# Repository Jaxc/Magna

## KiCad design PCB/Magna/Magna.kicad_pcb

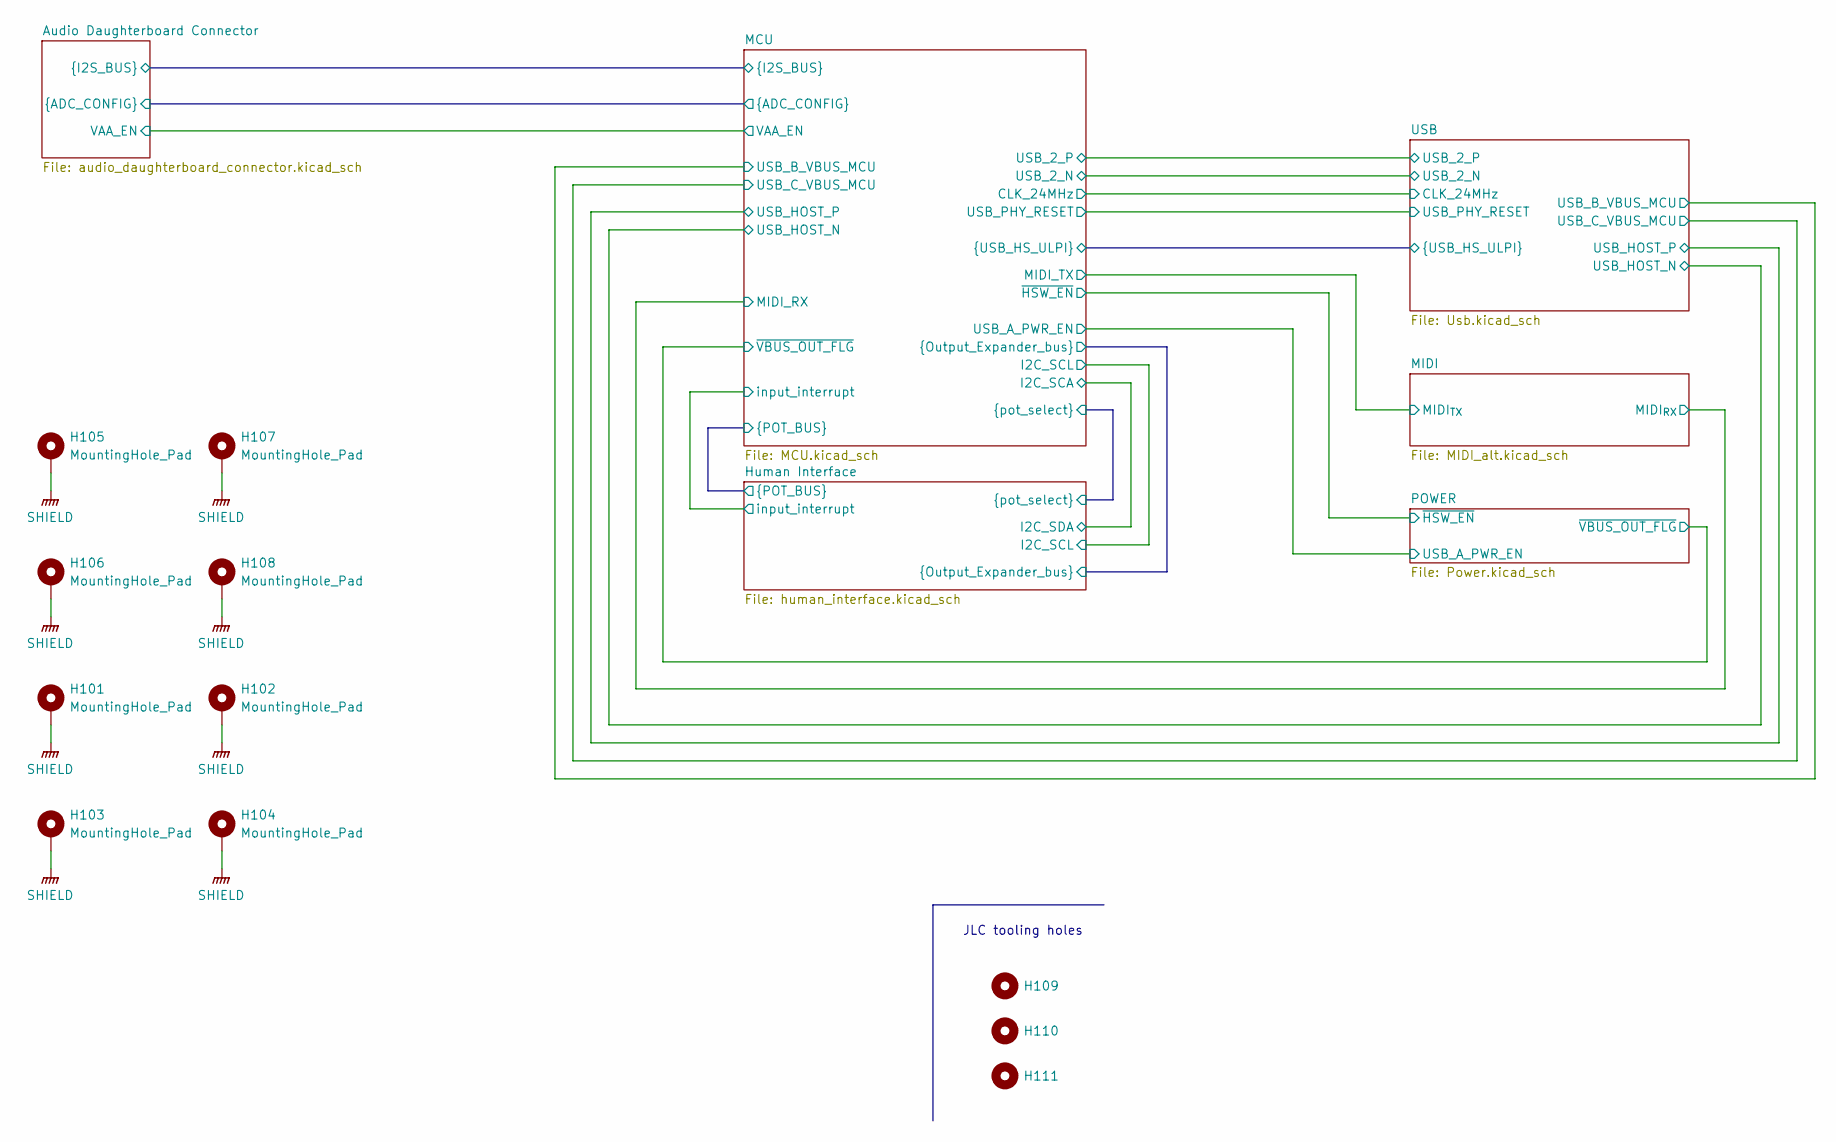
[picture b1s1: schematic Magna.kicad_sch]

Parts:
H101, H102, H103, H104, H105, H106, H107, H108: MountingHole_Pad; MountingHole_3.2mm_M3_Pad_Via
H109, H110, H111: MountingHole; ToolingHole_1.152mm

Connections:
SHIELD: H101.1, H102.1, H103.1, H104.1, H105.1, H106.1, H107.1, H108.1; also elsewhere on the board

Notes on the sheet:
JLC tooling holes

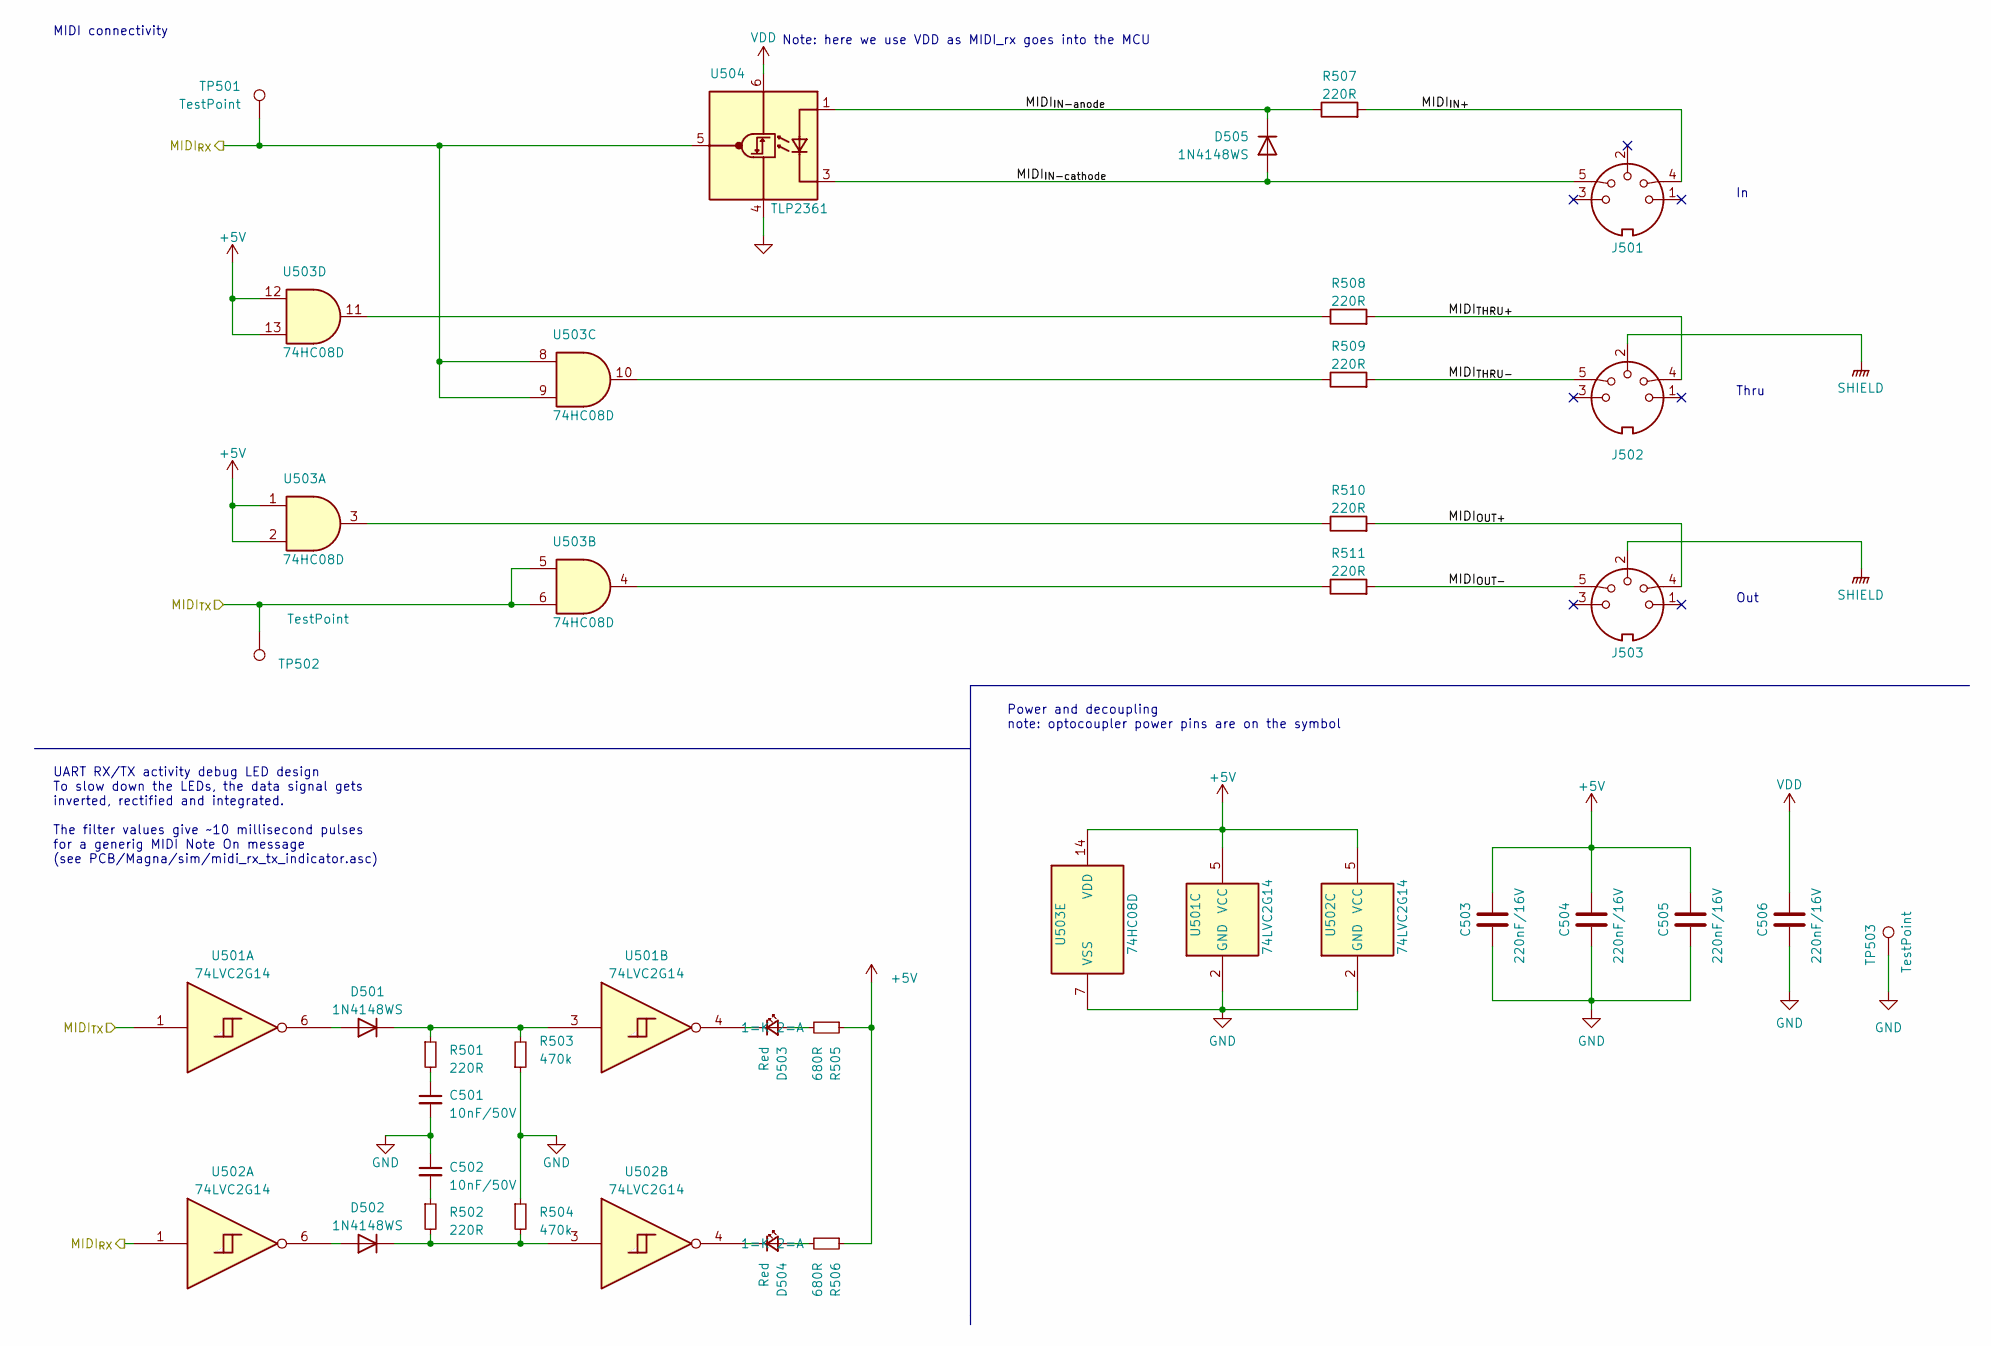
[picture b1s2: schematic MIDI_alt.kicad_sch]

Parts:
C501, C502: 10nF/50V; C_0805_2012Metric_Pad1.18x1.45mm_HandSolder; LCSC C1710
C503, C504, C505, C506: 220nF/16V; C_0402_1005Metric_Pad0.74x0.62mm_HandSolder; LCSC C16772
D501, D502, D505: 1N4148WS; D_SOD-523; LCSC C81598
D503, D504: Red; D_0805_2012Metric_Pad1.15x1.40mm_HandSolder; LCSC C84256
J501, J502, J503: DIN-5_180degree; DIN-504-M10; LCSC C2939344
R501, R502, R507, R508, R509, R510, R511: 220R; R_0805_2012Metric_Pad1.20x1.40mm_HandSolder; LCSC C17557
R503, R504: 470k; R_0805_2012Metric_Pad1.20x1.40mm_HandSolder; LCSC C17709
R505, R506: 680R; R_0805_2012Metric_Pad1.20x1.40mm_HandSolder; LCSC C17798
TP501, TP502, TP503: TestPoint; TestPoint_Keystone_5000-5004_Miniature
U501, U502: 74LVC2G14; SOT-363_SC-70-6_Handsoldering; LCSC C362110
U503: 74HC08D; SOIC-14_3.9x8.7mm_P1.27mm; LCSC C5593
U504: TLP2361; SO-6L_10x3.84mm_P1.27mm; LCSC C107626

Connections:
+5V: C503.1, C504.1, C505.1, R505.1, R506.1, U501.5 (VCC), U502.5 (VCC), U503.1, U503.2, U503.12, U503.13, U503.14 (VDD); also elsewhere on the board
/MCU/MIDI_RX: TP501.1, U502.1, U503.8, U503.9, U504.5 (VO); also elsewhere on the board
/MCU/MIDI_TX: TP502.1, U501.1, U503.5, U503.6; also elsewhere on the board
/MIDI/MIDI_{IN+}: J501.4, R507.2
/MIDI/MIDI_{IN-anode}: D505.1 (K), R507.1, U504.1 (A)
/MIDI/MIDI_{IN-cathode}: D505.2 (A), J501.5, U504.3 (K)
/MIDI/MIDI_{OUT+}: J503.4, R510.2
/MIDI/MIDI_{OUT-}: J503.5, R511.2
/MIDI/MIDI_{THRU+}: J502.4, R508.2
/MIDI/MIDI_{THRU-}: J502.5, R509.2
GND: C501.2, C502.1, C503.2, C504.2, C505.2, C506.2, R503.1, R504.1, TP503.1, U501.2 (GND), U502.2 (GND), U503.7 (VSS), U504.4 (GND); also elsewhere on the board
unnamed: C501.1, R501.2
unnamed: C502.2, R502.1
unnamed: D501.2 (A), U501.6
unnamed: D501.1 (K), R501.1, R503.2, U501.3
unnamed: D502.2 (A), U502.6
unnamed: D502.1 (K), R502.2, R504.2, U502.3
unnamed: D503.2 (A), R505.2
unnamed: D503.1 (K), U501.4
unnamed: D504.2 (A), R506.2
unnamed: D504.1 (K), U502.4
unnamed: R508.1, U503.11
unnamed: R509.1, U503.10
unnamed: R510.1, U503.3
unnamed: R511.1, U503.4
SHIELD: J502.2, J503.2; also elsewhere on the board
VDD: C506.1, U504.6 (VDD); also elsewhere on the board

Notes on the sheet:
Power and decoupling note: optocoupler power pins are on the symbol
Note: here we use VDD as MIDI_rx goes into the MCU
Out
MIDI connectivity
UART RX/TX activity debug LED design To slow down the LEDs, the data signal gets inverted, rectified and integrated. The filter values give ~10 millisecond pulses for a generig MIDI Note On message (see PCB/Magna/sim/midi_rx_tx_indicator.asc)
Thru

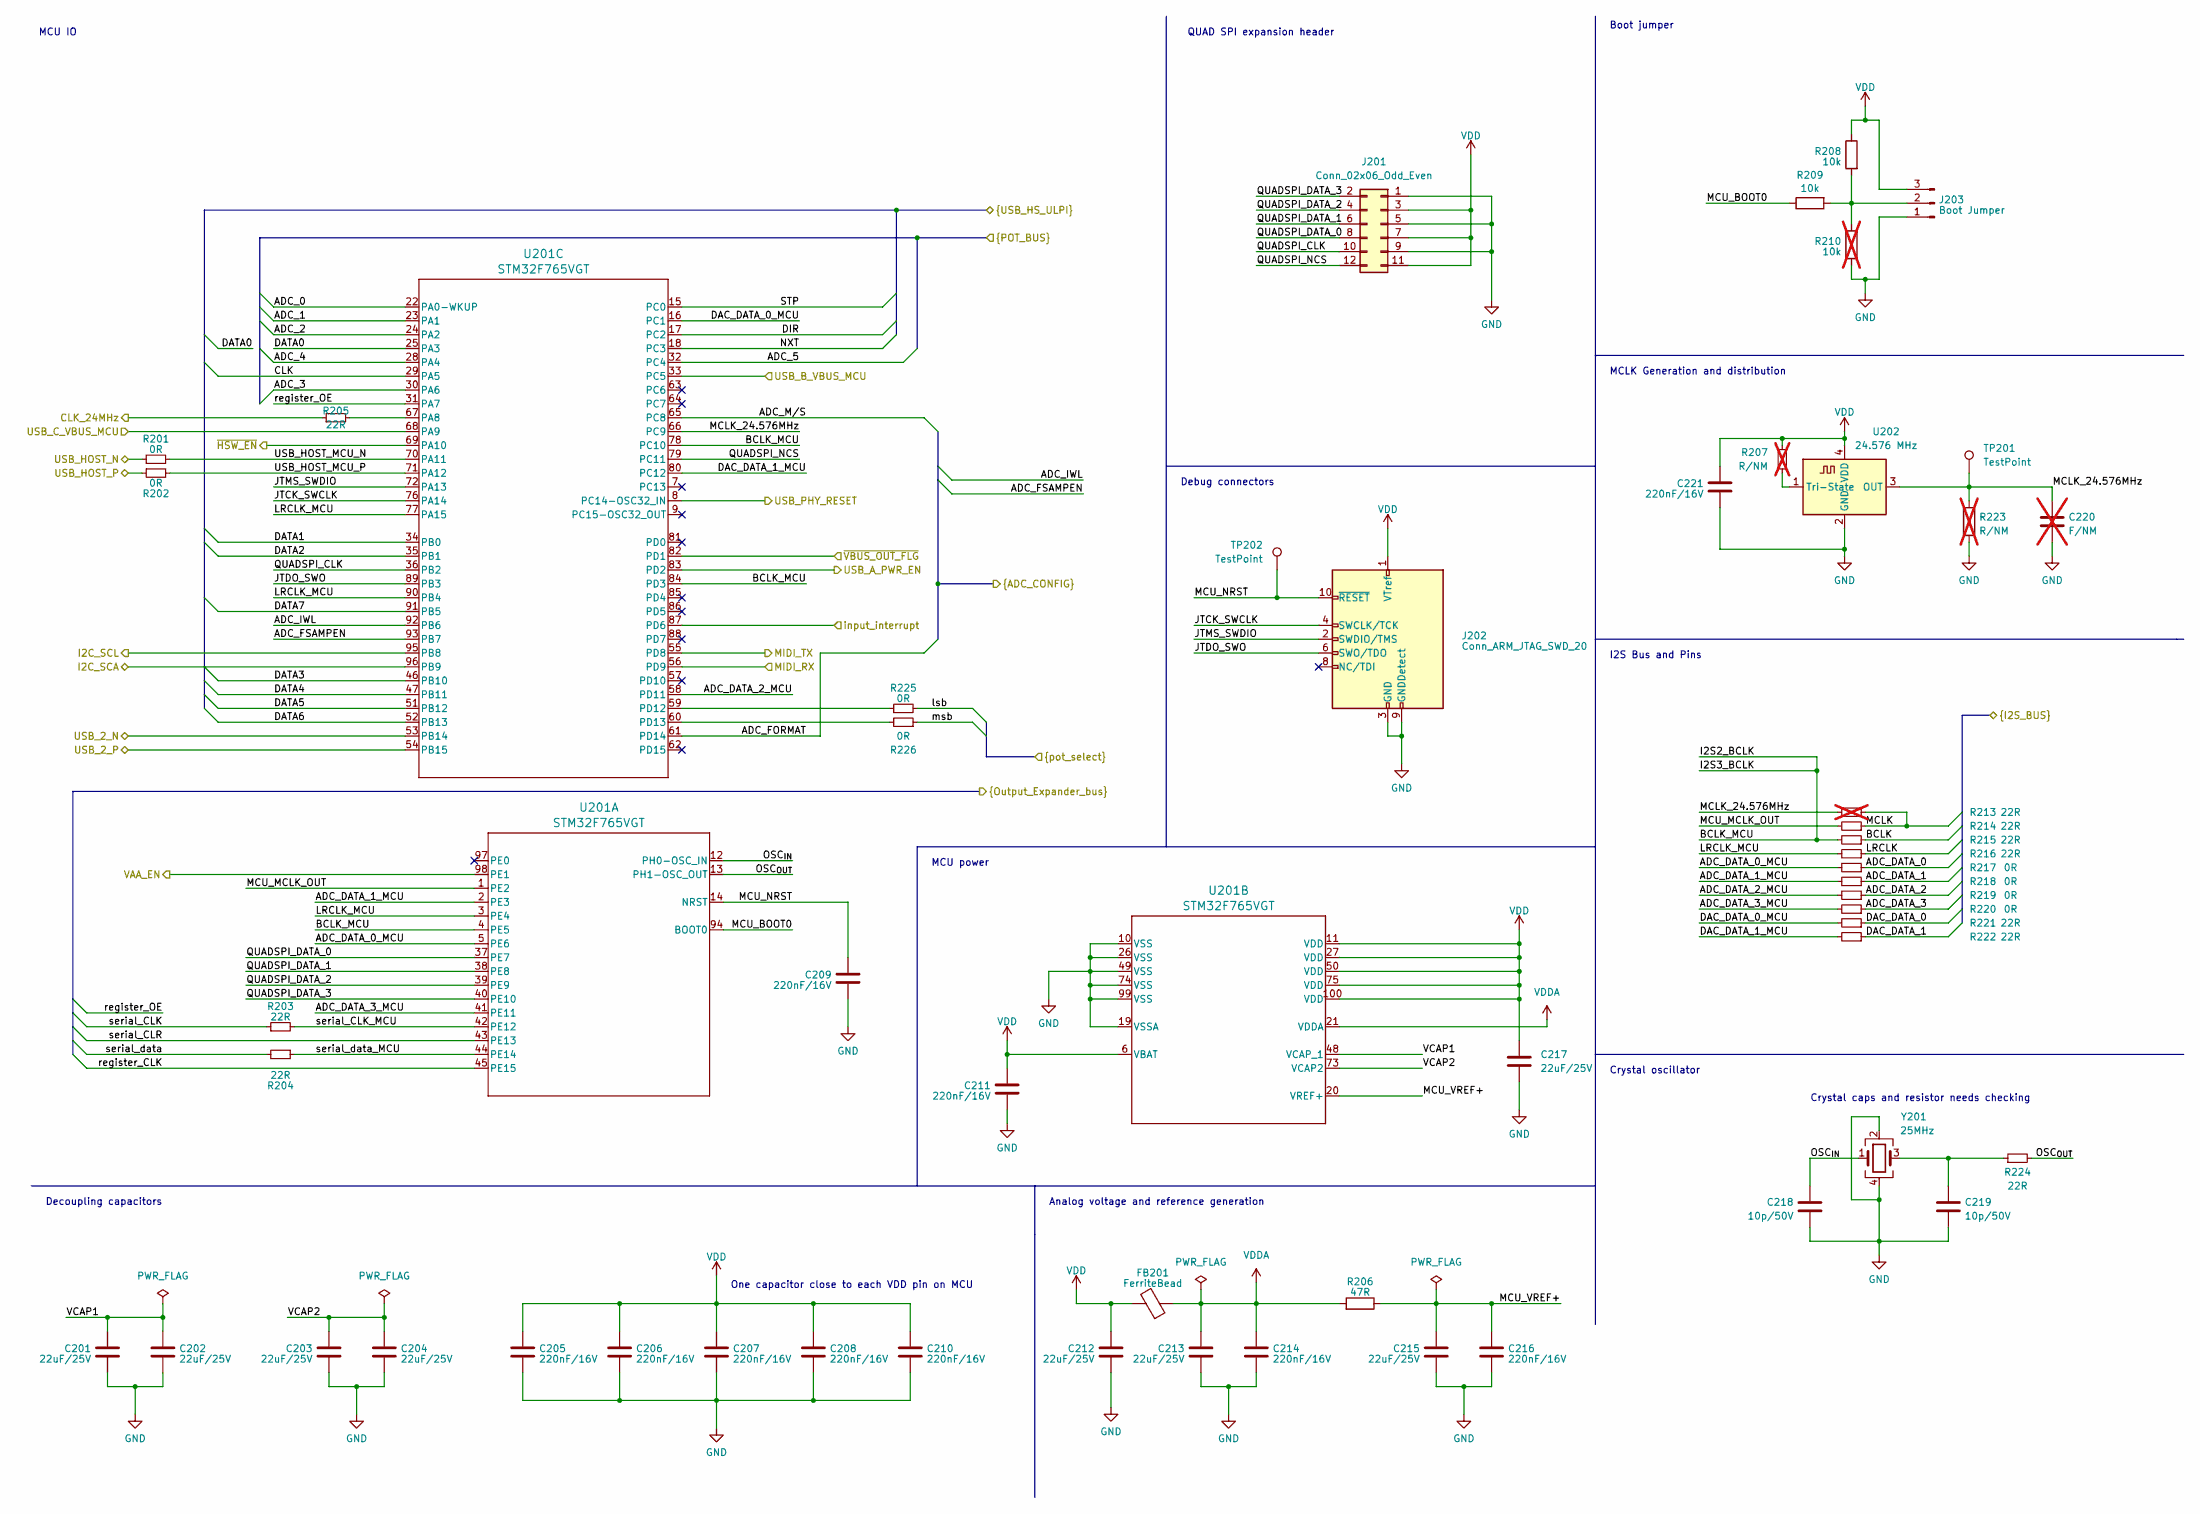
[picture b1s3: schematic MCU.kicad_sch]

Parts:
C201, C202, C203, C204, C212, C213, C215, C217: 22uF/25V; C_0805_2012Metric_Pad1.18x1.45mm_HandSolder; LCSC C45783
C205, C206, C207, C208, C209, C210, C211, C214, C216, C221: 220nF/16V; C_0402_1005Metric_Pad0.74x0.62mm_HandSolder; LCSC C16772
C218, C219: 10p/50V; C_0603_1608Metric_Pad1.08x0.95mm_HandSolder; LCSC C1634
C220: F/NM; C_0805_2012Metric_Pad1.18x1.45mm_HandSolder; not fitted
FB201: FerriteBead; L_0805_2012Metric; LCSC C1015
J201: Conn_02x06_Odd_Even; PinSocket_2x06_P2.54mm_Vertical_SMD; LCSC C2685123
J202: Conn_ARM_JTAG_SWD_20; PinHeader_2x05_P2.54mm_Vertical_SMD; LCSC C721865
J203: Boot Jumper; PinHeader_1x03_P2.54mm_Vertical
R201, R202, R217, R218, R219, R220, R225, R226: 0R; R_0805_2012Metric_Pad1.20x1.40mm_HandSolder; LCSC C17477
R203, R204, R205, R214, R215, R216, R221, R222, R224: 22R; R_0805_2012Metric_Pad1.20x1.40mm_HandSolder; LCSC C17561
R206: 47R; R_0805_2012Metric_Pad1.20x1.40mm_HandSolder; LCSC C17714
R207, R223: R/NM; R_0805_2012Metric_Pad1.20x1.40mm_HandSolder; not fitted
R208, R209: 10k; R_0805_2012Metric_Pad1.20x1.40mm_HandSolder; LCSC C17414
R210: 10k; R_0805_2012Metric_Pad1.20x1.40mm_HandSolder; LCSC C17414; not fitted
R213: 22R; R_0805_2012Metric_Pad1.20x1.40mm_HandSolder; LCSC C17561; not fitted
TP201, TP202: TestPoint; TestPoint_Keystone_5000-5004_Miniature
U201: STM32F765VGT; LQFP100-14x14mm; LCSC C435845
U202: 24.576 MHz; Oscillator_SMD_ECS_2520MV-xxx-xx-4Pin_2.5x2.0mm; LCSC C5203547
Y201: 25MHz; Crystal_SMD_3225-4Pin_3.2x2.5mm_HandSoldering; LCSC C9006

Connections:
/Audio Daughterboard Connector/ADC_DATA_0: R217.1; also elsewhere on the board
/Audio Daughterboard Connector/ADC_DATA_1: R218.1; also elsewhere on the board
/Audio Daughterboard Connector/ADC_DATA_2: R219.1; also elsewhere on the board
/Audio Daughterboard Connector/ADC_DATA_3: R220.1; also elsewhere on the board
/Audio Daughterboard Connector/ADC_FORMAT: U201.61 (PD14); also elsewhere on the board
/Audio Daughterboard Connector/ADC_FSAMPEN: U201.93 (PB7); also elsewhere on the board
/Audio Daughterboard Connector/ADC_IWL: U201.92 (PB6); also elsewhere on the board
/Audio Daughterboard Connector/ADC_M/S: U201.65 (PC8); also elsewhere on the board
/Audio Daughterboard Connector/BCLK: R215.1; also elsewhere on the board
/Audio Daughterboard Connector/DAC_DATA_0: R221.1; also elsewhere on the board
/Audio Daughterboard Connector/DAC_DATA_1: R222.1; also elsewhere on the board
/Audio Daughterboard Connector/LRCLK: R216.1; also elsewhere on the board
/Audio Daughterboard Connector/MCLK: R213.1, R214.1; also elsewhere on the board
/Audio Daughterboard Connector/VAA_EN: U201.98 (PE1); also elsewhere on the board
/Human Interface/ADC_0: U201.22 (PA0-WKUP); also elsewhere on the board
/Human Interface/ADC_1: U201.23 (PA1); also elsewhere on the board
/Human Interface/ADC_2: U201.24 (PA2); also elsewhere on the board
/Human Interface/ADC_3: U201.30 (PA6); also elsewhere on the board
/Human Interface/ADC_4: U201.28 (PA4); also elsewhere on the board
/Human Interface/ADC_5: U201.32 (PC4); also elsewhere on the board
/Human Interface/I2C_SCL: U201.95 (PB8); also elsewhere on the board
/Human Interface/I2C_SDA: U201.96 (PB9); also elsewhere on the board
/Human Interface/input_interrupt: U201.87 (PD6); also elsewhere on the board
/Human Interface/lsb: R225.2; also elsewhere on the board
/Human Interface/msb: R226.1; also elsewhere on the board
/Human Interface/register_CLK: U201.45 (PE15); also elsewhere on the board
/Human Interface/register_OE: U201.31 (PA7); also elsewhere on the board
/Human Interface/serial_CLK: R203.1; also elsewhere on the board
/Human Interface/serial_CLR: U201.43 (PE13); also elsewhere on the board
/Human Interface/serial_data: R204.2; also elsewhere on the board
/MCU/ADC_DATA_0_MCU: R217.2, U201.5 (PE6)
/MCU/ADC_DATA_1_MCU: R218.2, U201.2 (PE3)
/MCU/ADC_DATA_2_MCU: R219.2, U201.58 (PD11)
/MCU/ADC_DATA_3_MCU: R220.2, U201.41 (PE11)
/MCU/BCLK_MCU: R215.2, U201.4 (PE5), U201.78 (PC10), U201.84 (PD3)
/MCU/CLK: U201.29 (PA5); also elsewhere on the board
/MCU/CLK_24MHz: R205.1; also elsewhere on the board
/MCU/DAC_DATA_0_MCU: R221.2, U201.16 (PC1)
/MCU/DAC_DATA_1_MCU: R222.2, U201.80 (PC12)
/MCU/DATA0: U201.25 (PA3); also elsewhere on the board
/MCU/DATA1: U201.34 (PB0); also elsewhere on the board
/MCU/DATA2: U201.35 (PB1); also elsewhere on the board
/MCU/DATA3: U201.46 (PB10); also elsewhere on the board
/MCU/DATA4: U201.47 (PB11); also elsewhere on the board
/MCU/DATA5: U201.51 (PB12); also elsewhere on the board
/MCU/DATA6: U201.52 (PB13); also elsewhere on the board
/MCU/DATA7: U201.91 (PB5); also elsewhere on the board
/MCU/DIR: U201.17 (PC2); also elsewhere on the board
/MCU/JTCK_SWCLK: J202.4 (SWCLK/TCK), U201.76 (PA14)
/MCU/JTDO_SWO: J202.6 (SWO/TDO), U201.89 (PB3)
/MCU/JTMS_SWDIO: J202.2 (SWDIO/TMS), U201.72 (PA13)
/MCU/LRCLK_MCU: R216.2, U201.3 (PE4), U201.77 (PA15), U201.90 (PB4)
/MCU/MCLK_24.576MHz: C220.1, R213.2, R223.1, TP201.1, U201.66 (PC9), U202.3 (OUT)
/MCU/MCU_BOOT0: R209.1, U201.94 (BOOT0)
/MCU/MCU_MCLK_OUT: R214.2, U201.1 (PE2)
/MCU/MCU_NRST: C209.1, J202.10 (~RESET), TP202.1, U201.14 (NRST)
/MCU/MCU_VREF+: C215.1, C216.1, R206.1, U201.20 (VREF+)
/MCU/MIDI_RX: U201.56 (PD9); also elsewhere on the board
/MCU/MIDI_TX: U201.55 (PD8); also elsewhere on the board
/MCU/NXT: U201.18 (PC3); also elsewhere on the board
/MCU/OSC_{IN}: C218.2, U201.12 (PH0-OSC_IN), Y201.1
/MCU/OSC_{OUT}: R224.2, U201.13 (PH1-OSC_OUT)
/MCU/QUADSPI_CLK: J201.10, U201.36 (PB2)
/MCU/QUADSPI_DATA_0: J201.8, U201.37 (PE7)
/MCU/QUADSPI_DATA_1: J201.6, U201.38 (PE8)
/MCU/QUADSPI_DATA_2: J201.4, U201.39 (PE9)
/MCU/QUADSPI_DATA_3: J201.2, U201.40 (PE10)
/MCU/QUADSPI_NCS: J201.12, U201.79 (PC11)
/MCU/STP: U201.15 (PC0); also elsewhere on the board
/MCU/USB_2_N: U201.53 (PB14); also elsewhere on the board
/MCU/USB_2_P: U201.54 (PB15); also elsewhere on the board
/MCU/USB_A_PWR_EN: U201.83 (PD2); also elsewhere on the board
/MCU/USB_B_VBUS_MCU: U201.33 (PC5); also elsewhere on the board
/MCU/USB_C_VBUS_MCU: U201.68 (PA9); also elsewhere on the board
/MCU/USB_HOST_MCU_N: R201.2, U201.70 (PA11)
/MCU/USB_HOST_MCU_P: R202.2, U201.71 (PA12)
/MCU/USB_PHY_RESET: U201.8 (PC14-OSC32_IN); also elsewhere on the board
/MCU/VCAP1: C201.1, C202.1, U201.48 (VCAP_1)
/MCU/VCAP2: C203.1, C204.1, U201.73 (VCAP2)
/MCU/serial_CLK_MCU: R203.2, U201.42 (PE12)
/MCU/serial_data_MCU: R204.1, U201.44 (PE14)
/MCU/~HSW_EN: U201.69 (PA10)
/MCU/~VBUS_OUT_FLG: U201.82 (PD1); also elsewhere on the board
/USB/USB_HOST_N: R201.1; also elsewhere on the board
/USB/USB_HOST_P: R202.1; also elsewhere on the board
GND: C201.2, C202.2, C203.2, C204.2, C205.2, C206.2, C207.2, C208.2, C209.2, C210.2, C211.2, C212.2, C213.2, C214.2, C215.2, C216.2, C217.2, C218.1, C219.2, C220.2, C221.2, J201.1, J201.5, J201.9, J202.3 (GND), J202.5 (GND), J202.9 (GNDDetect), J203.1, R210.2, R223.2, U201.10 (VSS), U201.19 (VSSA), U201.26 (VSS), U201.49 (VSS), U201.74 (VSS), U201.99 (VSS), U202.2 (GND), Y201.2, Y201.4; also elsewhere on the board
unnamed: C219.1, R224.1, Y201.3
unnamed: J203.2, R208.2, R209.2, R210.1
unnamed: R205.2, U201.67 (PA8)
unnamed: R225.1, U201.59 (PD12)
unnamed: R226.2, U201.60 (PD13)
unnamed: R207.2, U202.1 (Tri-State)
VDD: C205.1, C206.1, C207.1, C208.1, C210.1, C211.1, C212.1, C217.1, C221.1, FB201.2, J201.3, J201.7, J201.11, J202.1 (VTref), J203.3, R207.1, R208.1, U201.6 (VBAT), U201.11 (VDD), U201.27 (VDD), U201.50 (VDD), U201.75 (VDD), U201.100 (VDD), U202.4 (VDD); also elsewhere on the board
VDDA: C213.1, C214.1, FB201.1, R206.2, U201.21 (VDDA); also elsewhere on the board

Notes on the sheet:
Decoupling capacitors
Debug connectors
QUAD SPI expansion header
Boot jumper
MCU IO
Analog voltage and reference generation
Crystal caps and resistor needs checking
I2S Bus and Pins
MCU power
One capacitor close to each VDD pin on MCU
Crystal oscillator
MCLK Generation and distribution

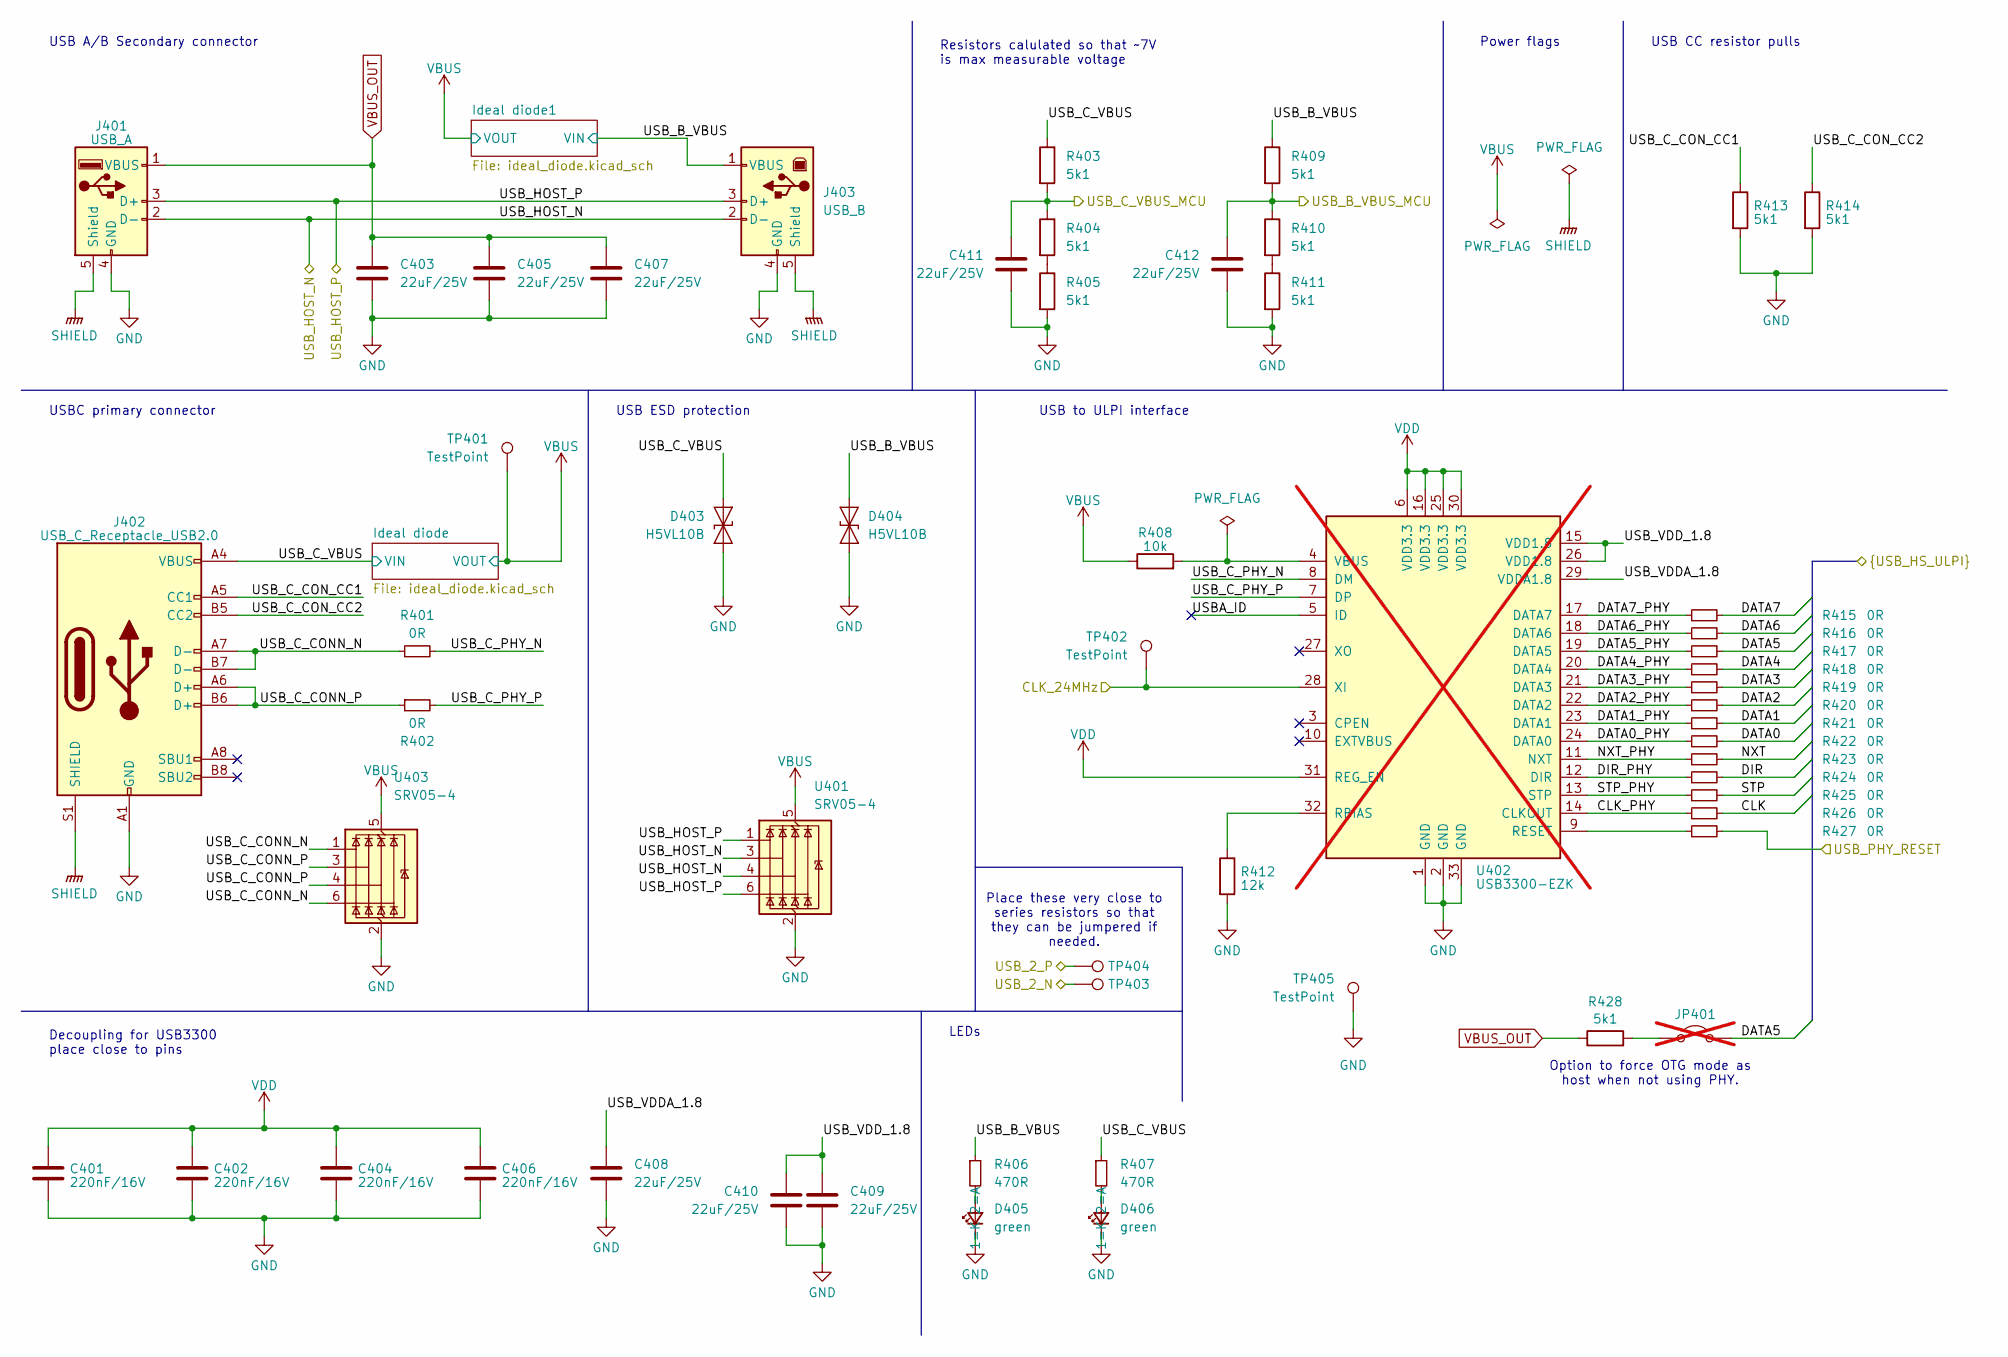
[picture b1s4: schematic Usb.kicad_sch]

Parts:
C401, C402, C404, C406: 220nF/16V; C_0402_1005Metric_Pad0.74x0.62mm_HandSolder; LCSC C16772
C403, C405, C407, C408, C409, C410, C411, C412: 22uF/25V; C_0805_2012Metric_Pad1.18x1.45mm_HandSolder; LCSC C45783
D403, D404: H5VL10B; D_SMB_Handsoldering; LCSC C78395
D405, D406: green; D_0805_2012Metric_Pad1.15x1.40mm_HandSolder; LCSC C2297
J401: USB_A; USB_A_Molex_67643_Horizontal; LCSC C456018
J402: USB_C_Receptacle_USB2.0; USB_C_Receptacle_G-Switch_GT-USB-7010ASV; LCSC C2982555
J403: USB_B; USB_B_OST_USB-B1HSxx_Horizontal; LCSC C720549
JP401: Jumper_2_Open; TestPoint_2Pads_Pitch2.54mm_Drill0.8mm; not fitted
R401, R402, R415, R416, R417, R418, R419, R420, R421, R422, R423, R424, R425, R426, R427: 0R; R_0805_2012Metric_Pad1.20x1.40mm_HandSolder; LCSC C17477
R403, R404, R405, R409, R410, R411, R413, R414, R428: 5k1; R_0805_2012Metric_Pad1.20x1.40mm_HandSolder; LCSC C27834
R406, R407: 470R; R_0805_2012Metric_Pad1.20x1.40mm_HandSolder; LCSC C17710
R408: 10k; R_0805_2012Metric_Pad1.20x1.40mm_HandSolder; LCSC C17414
R412: 12k; R_0805_2012Metric_Pad1.20x1.40mm_HandSolder; LCSC C17444
TP401, TP402, TP405: TestPoint; TestPoint_Keystone_5000-5004_Miniature
TP403, TP404: TestPoint; PinHeader_1x01_P1.00mm_Vertical
U401, U403: SRV05-4; SOT-23-6; LCSC C7420376
U402: USB3300-EZK; QFN-32-1EP_5x5mm_P0.5mm_EP3.45x3.45mm; LCSC C108383; not fitted

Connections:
/MCU/CLK: R426.2; also elsewhere on the board
/MCU/CLK_24MHz: TP402.1, U402.28 (XI); also elsewhere on the board
/MCU/DATA0: R422.2; also elsewhere on the board
/MCU/DATA1: R421.2; also elsewhere on the board
/MCU/DATA2: R420.2; also elsewhere on the board
/MCU/DATA3: R419.2; also elsewhere on the board
/MCU/DATA4: R418.2; also elsewhere on the board
/MCU/DATA5: JP401.2 (B), R417.2; also elsewhere on the board
/MCU/DATA6: R416.2; also elsewhere on the board
/MCU/DATA7: R415.2; also elsewhere on the board
/MCU/DIR: R424.2; also elsewhere on the board
/MCU/NXT: R423.2; also elsewhere on the board
/MCU/STP: R425.2; also elsewhere on the board
/MCU/USB_2_N: TP403.1; also elsewhere on the board
/MCU/USB_2_P: TP404.1; also elsewhere on the board
/MCU/USB_B_VBUS_MCU: C412.1, R409.2, R410.1; also elsewhere on the board
/MCU/USB_C_VBUS_MCU: C411.1, R403.2, R404.1; also elsewhere on the board
/MCU/USB_PHY_RESET: R427.2; also elsewhere on the board
/USB/CLK_PHY: R426.1, U402.14 (CLKOUT)
/USB/DATA0_PHY: R422.1, U402.24 (DATA0)
/USB/DATA1_PHY: R421.1, U402.23 (DATA1)
/USB/DATA2_PHY: R420.1, U402.22 (DATA2)
/USB/DATA3_PHY: R419.1, U402.21 (DATA3)
/USB/DATA4_PHY: R418.1, U402.20 (DATA4)
/USB/DATA5_PHY: R417.1, U402.19 (DATA5)
/USB/DATA6_PHY: R416.1, U402.18 (DATA6)
/USB/DATA7_PHY: R415.1, U402.17 (DATA7)
/USB/DIR_PHY: R424.1, U402.12 (DIR)
/USB/NXT_PHY: R423.1, U402.11 (NXT)
/USB/STP_PHY: R425.1, U402.13 (STP)
/USB/USBA_ID: U402.5 (ID)
/USB/USB_B_VBUS: D404.2 (A2), J403.1 (VBUS), R406.1, R409.1; also elsewhere on the board
/USB/USB_C_CONN_N: J402.A7 (D-), J402.B7 (D-), R401.1, U403.1 (I/O1), U403.6 (I/O4)
/USB/USB_C_CONN_P: J402.A6 (D+), J402.B6 (D+), R402.1, U403.3 (I/O2), U403.4 (I/O3)
/USB/USB_C_CON_CC1: J402.A5 (CC1), R413.1
/USB/USB_C_CON_CC2: J402.B5 (CC2), R414.1
/USB/USB_C_PHY_N: R401.2, U402.8 (DM)
/USB/USB_C_PHY_P: R402.2, U402.7 (DP)
/USB/USB_C_VBUS: D403.2 (A2), J402.A4 (VBUS), J402.A9 (VBUS), J402.B4 (VBUS), J402.B9 (VBUS), R403.1, R407.1; also elsewhere on the board
/USB/USB_HOST_N: J401.2 (D-), J403.2 (D-), U401.3 (I/O2), U401.4 (I/O3); also elsewhere on the board
/USB/USB_HOST_P: J401.3 (D+), J403.3 (D+), U401.1 (I/O1), U401.6 (I/O4); also elsewhere on the board
/USB/USB_VDDA_1.8: C408.1, U402.29 (VDDA1.8)
/USB/USB_VDD_1.8: C409.1, C410.1, U402.15 (VDD1.8), U402.26 (VDD1.8)
GND: C401.2, C402.2, C403.2, C404.2, C405.2, C406.2, C407.2, C408.2, C409.2, C410.2, C411.2, C412.2, D403.1 (A1), D404.1 (A1), D405.1 (K), D406.1 (K), J401.4 (GND), J402.A1 (GND), J402.A12 (GND), J402.B1 (GND), J402.B12 (GND), J403.4 (GND), R405.2, R411.2, R412.2, R413.2, R414.2, TP405.1, U401.2 (GND), U402.1 (GND), U402.2 (GND), U402.33 (GND), U403.2 (GND); also elsewhere on the board
unnamed: D405.2 (A), R406.2
unnamed: D406.2 (A), R407.2
unnamed: JP401.1 (A), R428.2
unnamed: R404.2, R405.1
unnamed: R410.2, R411.1
unnamed: R412.1, U402.32 (RBIAS)
unnamed: R427.1, U402.9 (RESET)
unnamed: R408.2, U402.4 (VBUS)
SHIELD: J401.5 (Shield), J402.S1 (SHIELD), J403.5 (Shield); also elsewhere on the board
VBUS: R408.1, TP401.1, U401.5 (VBUS), U403.5 (VBUS); also elsewhere on the board
VBUS_OUT: C403.1, C405.1, C407.1, J401.1 (VBUS), R428.1; also elsewhere on the board
VDD: C401.1, C402.1, C404.1, C406.1, U402.6 (VDD3.3), U402.16 (VDD3.3), U402.25 (VDD3.3), U402.30 (VDD3.3), U402.31 (REG_EN); also elsewhere on the board

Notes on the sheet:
Option to force OTG mode as host when not using PHY.
USB CC resistor pulls
Decoupling for USB3300 place close to pins
Place these very close to series resistors so that they can be jumpered if needed.
LEDs
USB A/B Secondary connector
USB ESD protection
Power flags
USBC primary connector
USB to ULPI interface
Resistors calulated so that ~7V is max measurable voltage
